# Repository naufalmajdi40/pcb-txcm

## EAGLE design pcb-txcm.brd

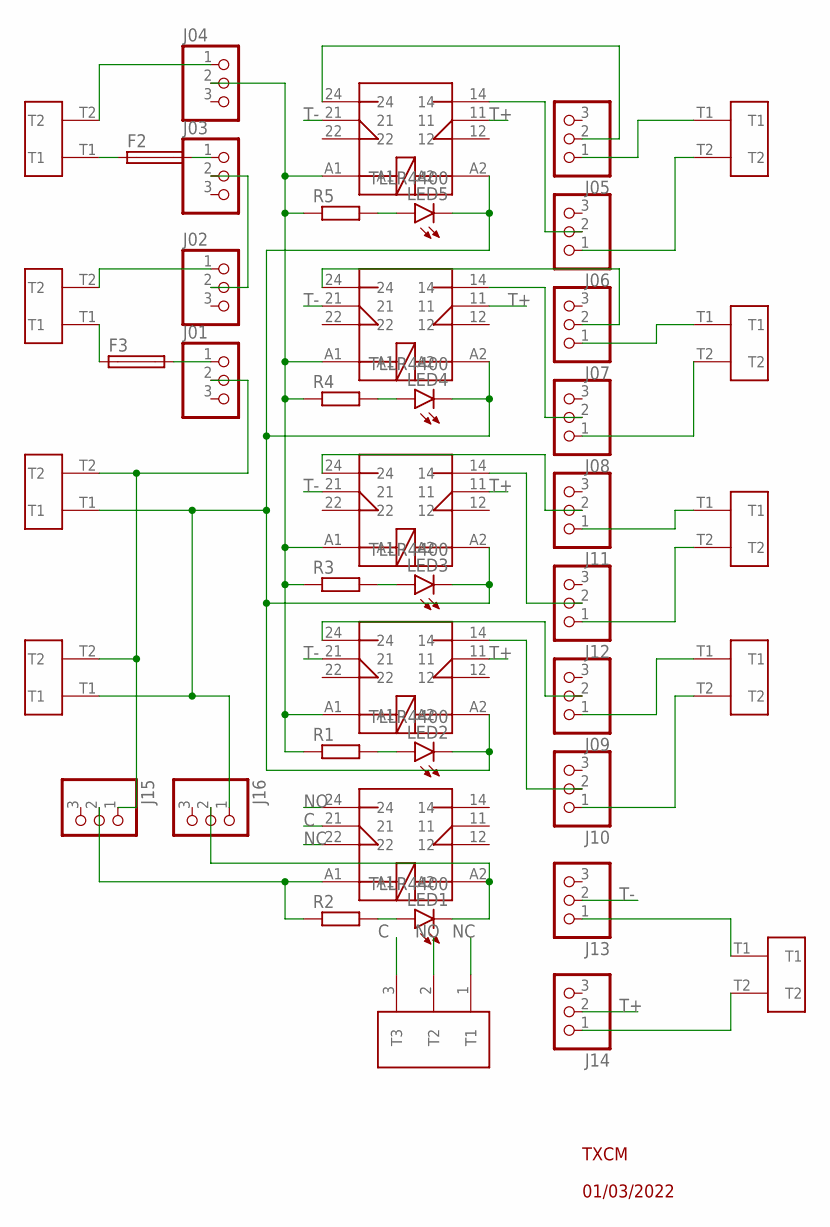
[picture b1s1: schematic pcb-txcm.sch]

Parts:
F2, F3: SH22,5A
J01, J02, J03, J04, J05, J06, J07, J08, J09, J10, J11, J12, J13, J14, J15, J16: PINHD-1X3; 1X03
LED1, LED2, LED3, LED4, LED5: TLLR4400; LED3MM
R1, R2, R3, R4, R5: R-EU_0309/12; 0309/12
RSB2A080ED1, RSB2A080ED2, RSB2A080ED3, RSB2A080ED4, RSB2A080ED5: RSB2A080ED
TB7.1, TB7.2, TB7.3, TB7.4, TB7.6, TB7.7, TB7.8, TB7.9, TB7.10: TB7.62
TB7.62-3P1: TB7.62-3P

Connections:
48V+: J16.1, LED2.K (C), LED3.K (C), LED4.K (C), LED5.K (C), RSB2A080ED1.A2, RSB2A080ED2.A2, RSB2A080ED3.A2, RSB2A080ED4.A2, TB7.3.T1, TB7.4.T1
48V-: J01.2, J15.1, TB7.3.T2, TB7.4.T2
C: RSB2A080ED5.21, TB7.62-3P1.3 (T3)
unnamed: J04.1, TB7.1.T2
unnamed: F2.1, TB7.1.T1
unnamed: J04.2, R1.1, R3.1, R4.1, R5.1, RSB2A080ED1.A1, RSB2A080ED2.A1, RSB2A080ED3.A1, RSB2A080ED4.A1
unnamed: J02.2, J03.2
unnamed: J02.1, TB7.2.T2
unnamed: F3.2, J01.1
unnamed: F3.1, TB7.2.T1
unnamed: F2.2, J03.1
unnamed: J15.2, R2.1, RSB2A080ED5.A1
unnamed: J16.2, LED1.K (C), RSB2A080ED5.A2
unnamed: J05.2, RSB2A080ED1.24
unnamed: J06.2, RSB2A080ED1.14
unnamed: J05.1, TB7.6.T1
unnamed: J06.1, TB7.6.T2
unnamed: J07.2, RSB2A080ED2.24
unnamed: J07.1, TB7.7.T1
unnamed: LED1.A, R2.2
unnamed: J08.1, TB7.7.T2
unnamed: J11.2, RSB2A080ED3.24
unnamed: J11.1, TB7.8.T1
unnamed: J12.2, RSB2A080ED3.14
unnamed: J12.1, TB7.8.T2
unnamed: J09.2, RSB2A080ED4.24
unnamed: J09.1, TB7.9.T1
unnamed: J10.2, RSB2A080ED4.14
unnamed: J10.1, TB7.9.T2
unnamed: LED2.A, R1.2
unnamed: LED3.A, R3.2
unnamed: J13.1, TB7.10.T1
unnamed: J14.1, TB7.10.T2
unnamed: LED4.A, R4.2
unnamed: LED5.A, R5.2
unnamed: J08.2, RSB2A080ED2.14
NC: RSB2A080ED5.22, TB7.62-3P1.1 (T1)
NO: RSB2A080ED5.24, TB7.62-3P1.2 (T2)
T+: J14.2, RSB2A080ED1.11, RSB2A080ED2.11, RSB2A080ED3.11, RSB2A080ED4.11
T-: J13.2, RSB2A080ED1.21, RSB2A080ED2.21, RSB2A080ED3.21, RSB2A080ED4.21

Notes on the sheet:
TXCM
01/03/2022

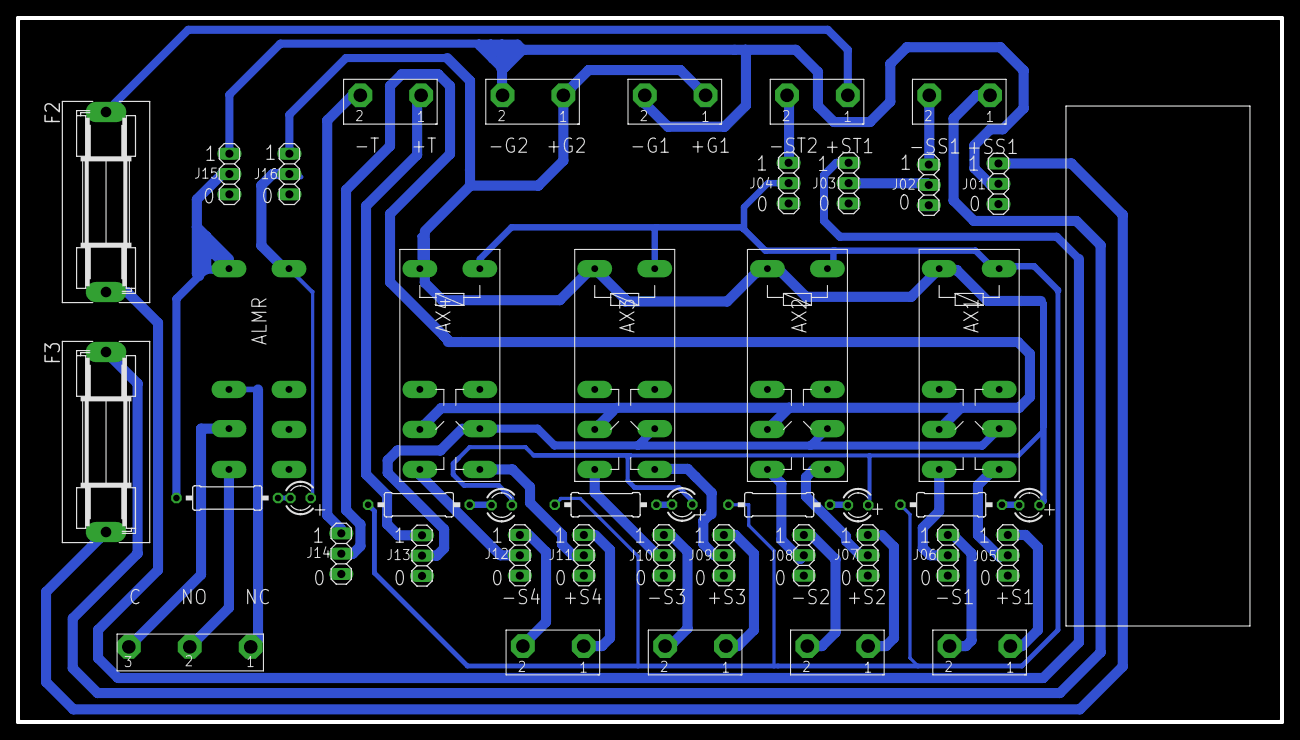
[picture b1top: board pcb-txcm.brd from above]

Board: 2 copper layers, 158.0 x 88.0 mm, 43 parts (1 on the bottom side), 40 nets.

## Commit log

2023-03-21 upload first
    percobaan upload
2023-03-21 Add files via upload
    Penambahan Logo Mel
